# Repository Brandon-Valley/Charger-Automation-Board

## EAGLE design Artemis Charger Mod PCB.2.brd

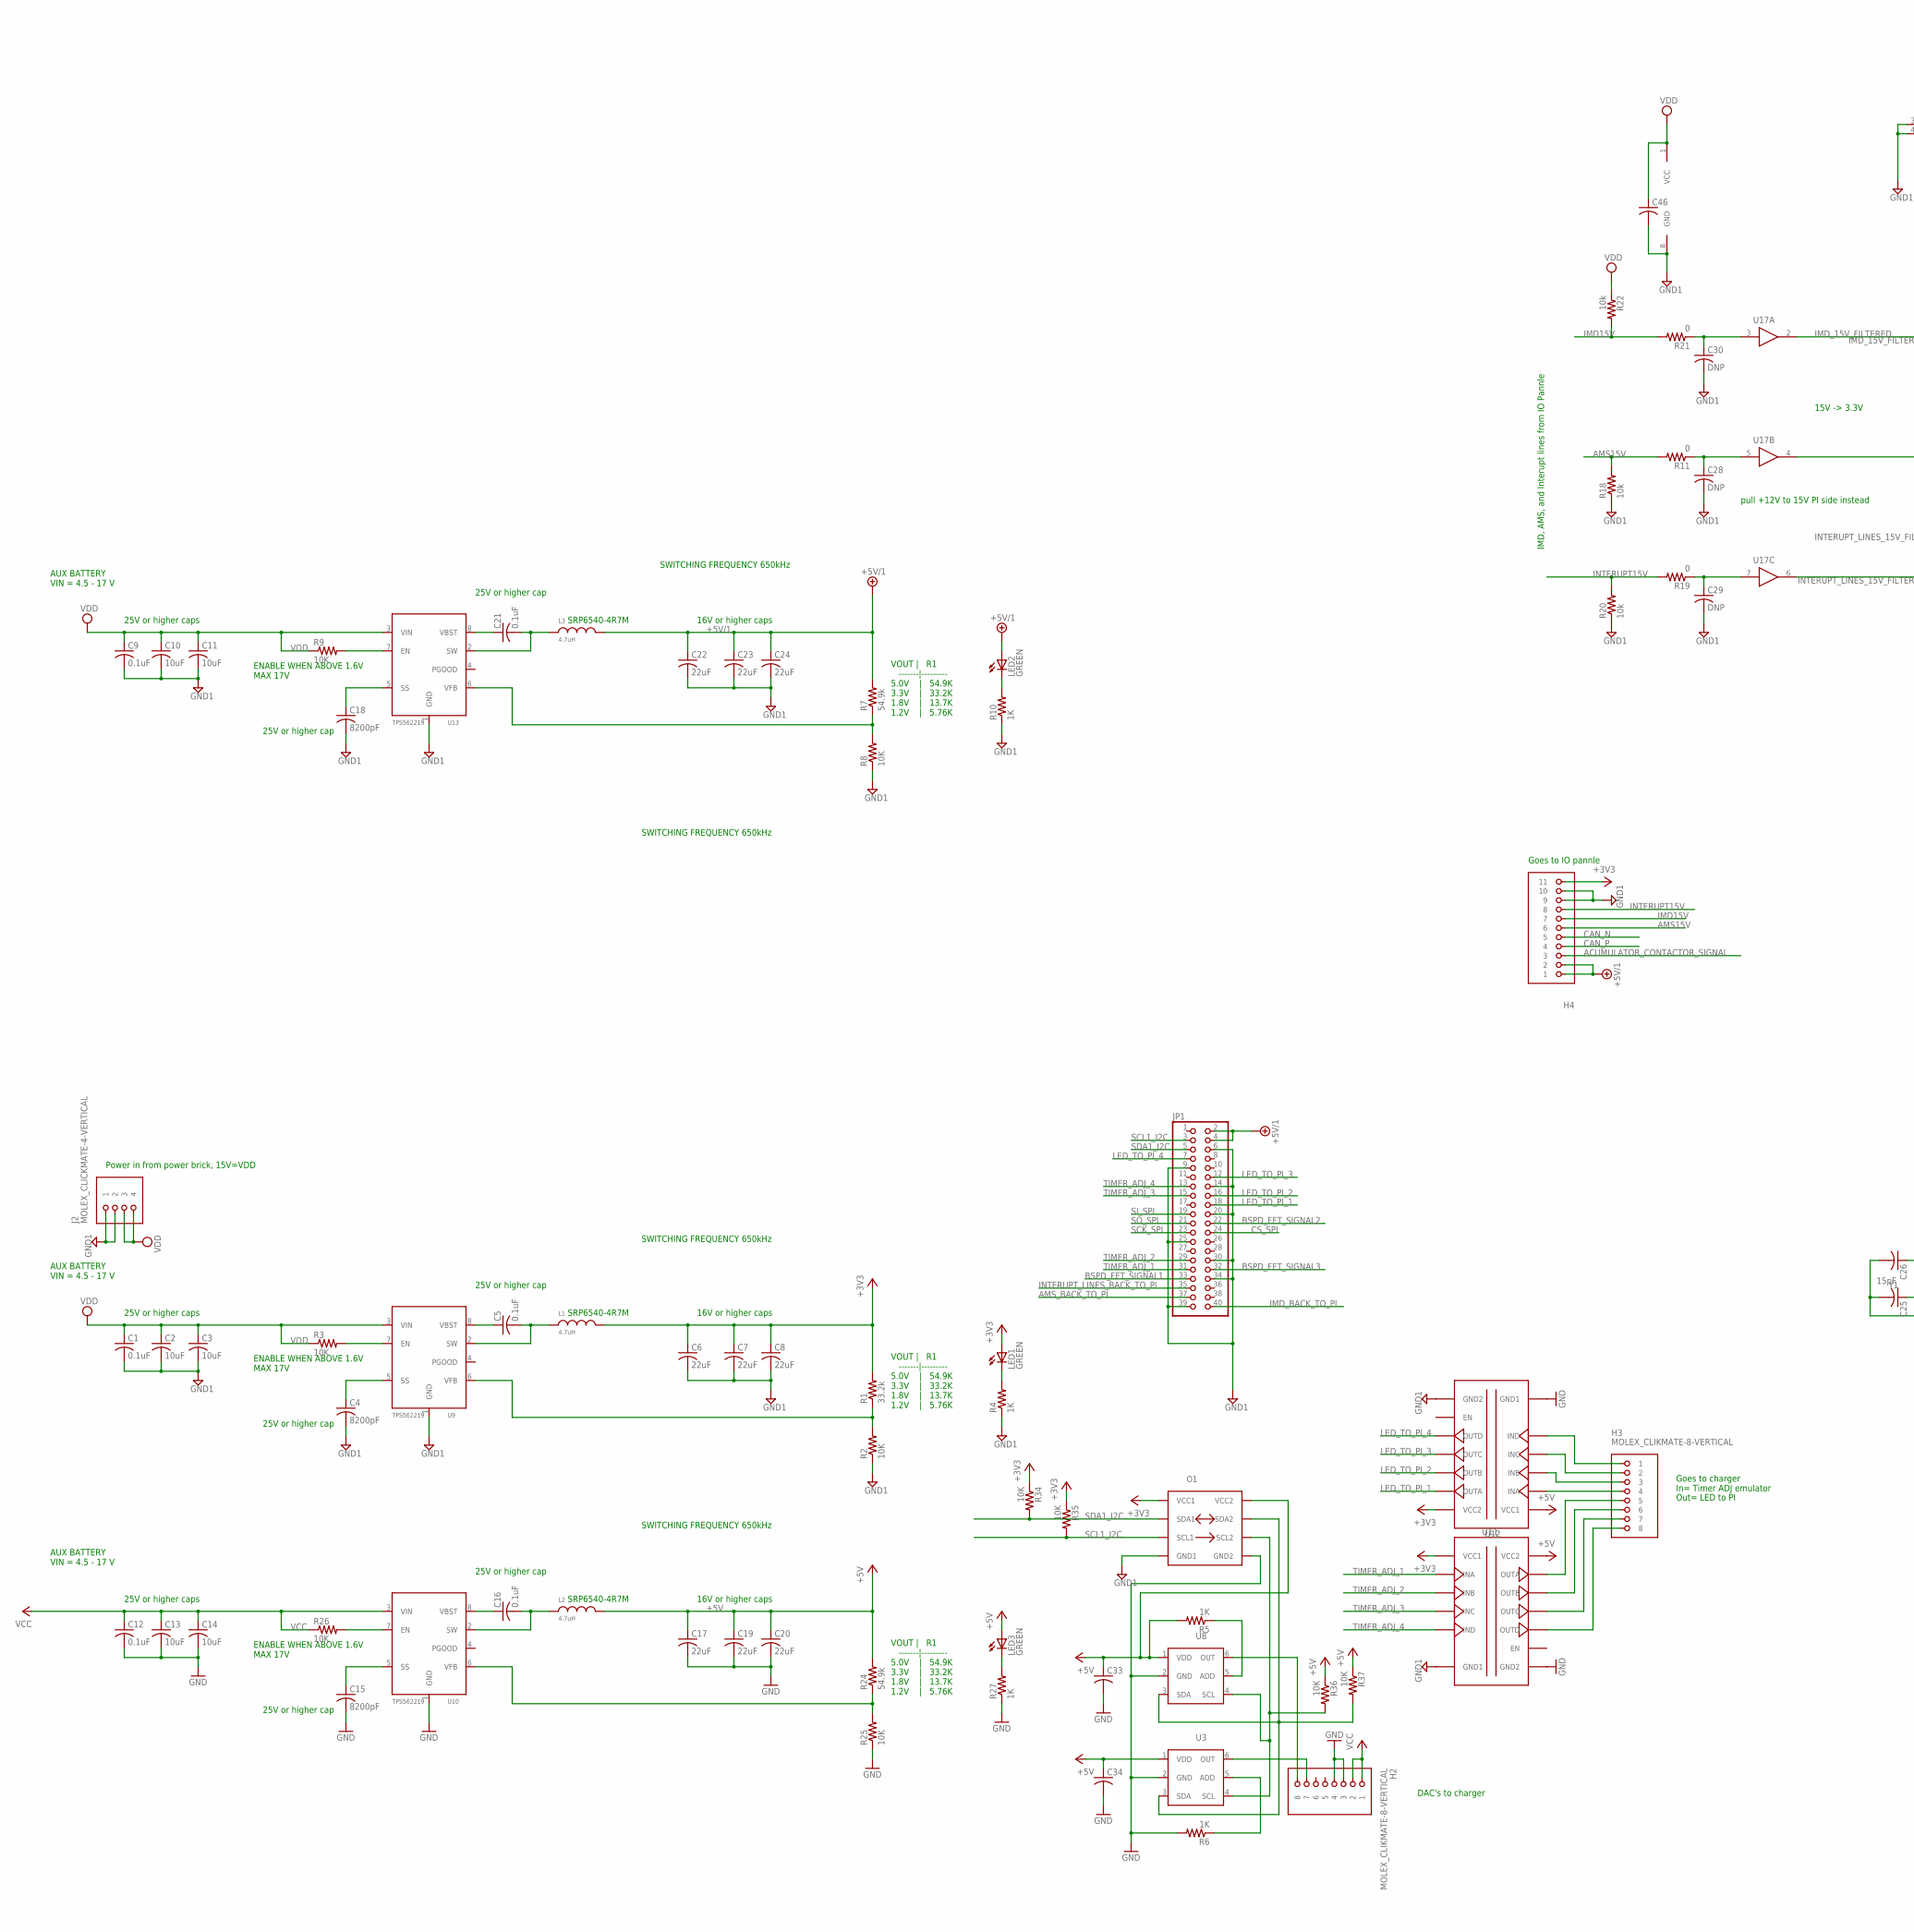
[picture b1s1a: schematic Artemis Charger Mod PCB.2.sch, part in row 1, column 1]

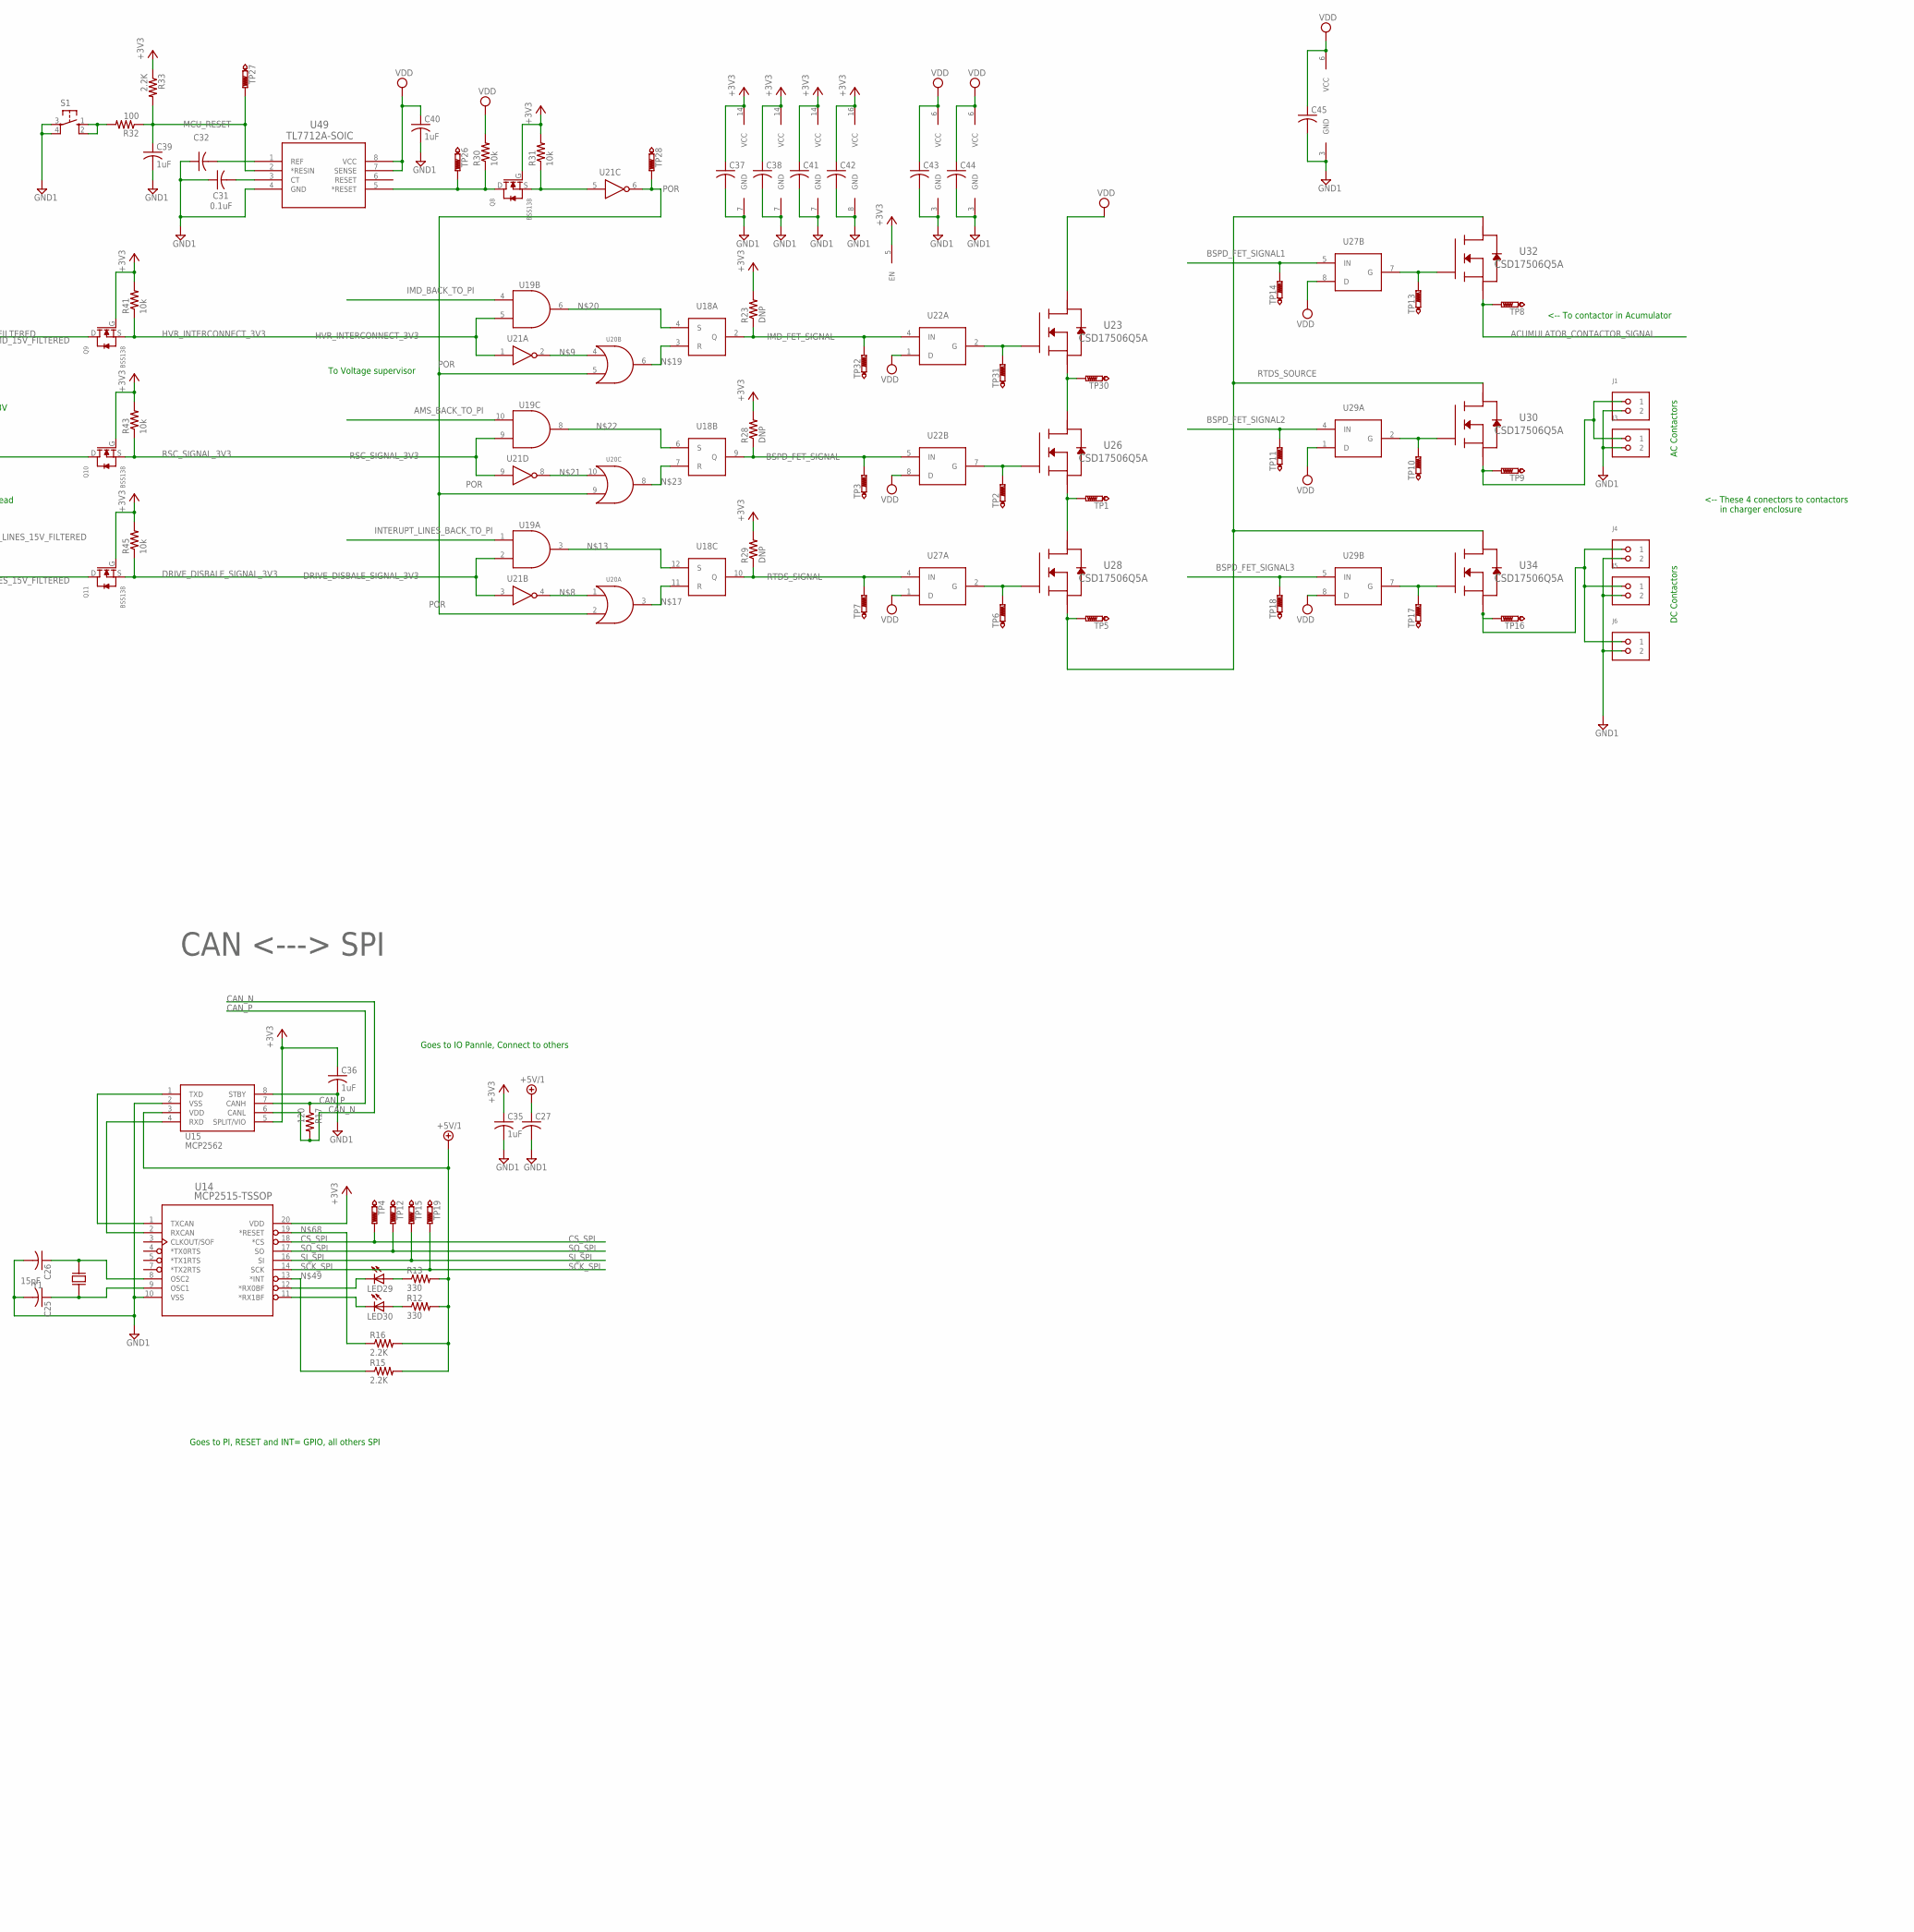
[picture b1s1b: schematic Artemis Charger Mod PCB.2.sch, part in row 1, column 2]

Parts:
C1, C5, C12, C16, C21: 0.1uF; C0805; PARTNO GRM21BR71E104KA01L
C2, C3, C10, C11, C13, C14: 10uF; C0805; PARTNO GRM21BR61E106KA73L
C4, C15, C18: 8200pF; C0805; PARTNO C0805C822K5RACTU
C6, C7, C8, C17, C19, C20, C22, C23, C24: 22uF; C0805; PARTNO C2012JB1E226M125AC
C9: 0.1uF; C0805; PARTNO 5025841170
C25, C26: 15pF; C0805; MPN 08051A150JAT2A
C27, C33, C34, C37, C38, C41, C42, C43, C44, C45, C46: 0.1uF; C0805; MPN C1005X7R1E104K050BB
C28, C29, C30: DNP; C0805
C31, C32: 0.1uF; C0805; MPN C2012X7R1H104K085AA
C35, C36, C39, C40: 1uF; C0805; PARTNO EMK212B7105KG-T
H2, H3: MOLEX_CLIKMATE-8-VERTICAL; MOLEX-CLIKMATE-8-VERTICAL-HEADER; PARTNO 5025840870
H4: MOLEX_CLICKMATE-11-VERTICAL-VERTICAL; MOLEX_CLICKMATE-11-VERTICAL-HEADER; PARTNO 5025841170
J1, J3, J4, J5, J6: MOLEX_CLICKMATE-2-VERTICAL; MOLEX-CLIKMATE-2-VERTICAL-HEADER; PARTNO 5025840270
J2: MOLEX_CLICKMATE-4-VERTICAL; MOLEX-CLIKMATE-4-VERTICAL-HEADER; PARTNO 5040500491
JP1: PINHD-2X20; 2X20; PARTNO 68602-220HLF
L1, L2, L3: 4.7uH; SRP6540; PARTNO SRP6540-4R7M
LED1, LED2, LED3: GREEN; CHIPLED_0805; PARTNO 598-8170-107F
LED29, LED30: LEDCHIP-LED0805; CHIP-LED0805; PARTNO 598-8170-107F
O1: ISO1541; PARTNO ISO1541DR
Q8, Q9, Q10, Q11: BSS138; PARTNO BSS138
R1: 33.2k; R0805; PARTNO 1676307-2
R2, R3, R8, R9, R25, R26, R34, R35, R36, R37: 10K; R0805; PARTNO ERJ-6ENF1002V
R4, R5, R6, R10, R27: 1K; R0805; PARTNO ERJ-6ENF1001V
R7, R24: 54.9k; R0805; PARTNO ERA-6AEB5492V
R11, R19, R21: 0; R0805; PARTNO ERJ-6GEY0R00V
R12, R13: 330; R0805; PARTNO ERJ-P6WF3300V
R15, R16, R33: 2.2K; R0805; PARTNO ERA-6AEB222V
R17: 120; R0805; PARTNO ERJ-6ENF1200V
R18, R20, R22, R30, R31, R41, R43, R45: 10k; R0805; PARTNO ERJ-6ENF1002V
R23, R28, R29: DNP; R0805
R32: 100; R0805; PARTNO ERJ-6ENF1000V
S1: TE-FSM4JSMATR; PARTNO FSM4JSMATR
TP1, TP2, TP3, TP4, TP5, TP6, TP7, TP8, TP9, TP10, TP11, TP12, TP13, TP14, TP15, TP16, TP17, TP18, TP19, TP26, TP27, TP28, TP30, TP31, TP32: PTR1TP20R; TP20R
U3, U8: MAX5812LEUT+TCT-ND; MAX5812; PARTNO MAX5812LEUT+T
U9, U10, U13: TPS562219; PARTNO TPS562219DDFT
U11, U12: ISO7340; ISO734X; PARTNO ISO7340CDWR
U14: MCP2515-TSSOP; TSSOP20_MC; MPN MCP2515-E/ST
U15: MCP2562; SOIC8-N_MC; MPN MCP2562-E/SN
U17: CD4050BD; SOIC-16; PARTNO CD4050BDR
U18: CD4043B; PW16-M; PARTNO CD4043BPWR
U19: SN74LVC08ASOIC; D14; PARTNO SN74LVC08ADR
U20: SN74LVC32ASOIC; D14; PARTNO SN74LVC32ADR
U21: SN74LVC04ASOIC; SOIC-14; PARTNO SN74LVC04ADR
U22, U27, U29: LTC1155; LT-SOL8; PARTNO LTC1155CS8#PBF
U23, U26, U28, U30, U32, U34: CSD17506Q5A; SON_5X6; PARTNO CSD17506Q5A
U49: TL7712A-SOIC; D8; MPN TL7705BID
Y1: CSM-3X; PARTNO ECS-160-20-3X-TR

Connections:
+3V3: C6.1, C7.1, C8.1, C35.1, C36.1, C37.1, C38.1, C41.1, C42.1, H4.11, L1.P$2, LED1.A, O1.1 (VCC1), Q8.G, Q9.G, Q10.G, Q11.G, R1.2, R23.2, R28.2, R29.2, R31.2, R33.1, R34.1, R35.1, R41.2, R43.2, R45.2, U11.P$1 (VCC1), U12.P$16 (VCC2), U14.20 (VDD), U15.5 (SPLIT/VIO), U18.5 (EN), U18.16 (VCC), U19.14 (VCC), U20.14 (VCC), U21.14 (VCC)
+5V: C17.1, C19.1, C20.1, C33.1, C34.1, L2.P$2, LED3.A, O1.8 (VCC2), R5.2, R24.2, R36.1, R37.1, U3.1 (VDD), U8.1 (VDD), U11.P$16 (VCC2), U12.P$1 (VCC1)
+5V/1: C22.1, C23.1, C24.1, C27.1, H4.1, H4.2, JP1.2, JP1.4, L3.P$2, LED2.A, R7.2, R12.2, R13.2, R15.2, R16.2, U15.3 (VDD)
ACUMULATOR_CONTACTOR_SIGNAL: H4.3, TP8.TP, U32.1 (S), U32.2 (S), U32.3 (S)
ADD: R6.1, U3.5 (ADD)
AMS15V: H4.6, R11.2, R18.2
AMS_15V_FILTERED: Q10.D, U17.4 (OUT)
AMS_BACK_TO_PI: JP1.37, U19.10 (IN1)
BSPD_FET_SIGNAL: R28.1, TP3.TP, U18.9 (Q), U22.5 (IN)
BSPD_FET_SIGNAL1: JP1.33, TP14.TP, U27.5 (IN)
BSPD_FET_SIGNAL2: JP1.22, TP11.TP, U29.4 (IN)
BSPD_FET_SIGNAL3: JP1.32, TP18.TP, U29.5 (IN)
CAN_N: H4.5, R17.2, U15.6 (CANL)
CAN_P: H4.4, R17.1, U15.7 (CANH)
CS_SPI: JP1.24, TP4.TP, U14.18 (*CS)
DRIVE_DISBALE_SIGNAL_3V3: Q11.S, R45.1, U19.2 (IN2), U21.3 (IN)
FET_CONNECT_1: TP30.TP, U23.1 (S), U23.2 (S), U23.3 (S), U26.5 (D), U26.6 (D), U26.7 (D), U26.8 (D), U26.PAD (D), U26.PAD1 (D), U26.VIA1 (D), U26.VIA2 (D), U26.VIA3 (D), U26.VIA4 (D), U26.VIA5 (D), U26.VIA6 (D), U26.VIA7 (D), U26.VIA8 (D), U26.VIA9 (D)
FET_CONNECT_2: TP1.TP, U26.1 (S), U26.2 (S), U26.3 (S), U28.5 (D), U28.6 (D), U28.7 (D), U28.8 (D), U28.PAD (D), U28.PAD1 (D), U28.VIA1 (D), U28.VIA2 (D), U28.VIA3 (D), U28.VIA4 (D), U28.VIA5 (D), U28.VIA6 (D), U28.VIA7 (D), U28.VIA8 (D), U28.VIA9 (D)
GND: C12.2, C13.2, C14.2, C15.2, C17.2, C19.2, C20.2, C33.2, C34.2, H2.3, H2.4, O1.5 (GND2), R6.2, R25.1, R27.1, U3.2 (GND), U8.2 (GND), U10.1 (GND), U11.P$9 (GND2), U11.P$15 (GND2), U12.P$2 (GND1), U12.P$8 (GND1)
GND1: C1.2, C2.2, C3.2, C4.2, C6.2, C7.2, C8.2, C9.2, C10.2, C11.2, C18.2, C22.2, C23.2, C24.2, C25.2, C26.2, C27.2, C28.2, C29.2, C30.2, C31.1, C32.1, C35.2, C36.2, C37.2, C38.2, C39.2, C40.2, C41.2, C42.2, C43.2, C44.2, C45.2, C46.2, H4.9, H4.10, J1.2, J2.1, J2.2, J3.2, J4.2, J5.2, J6.2, JP1.6, JP1.9, JP1.14, JP1.20, JP1.25, JP1.30, JP1.34, JP1.39, O1.4 (GND1), R2.1, R4.1, R8.1, R10.1, R18.1, R20.1, S1.3, S1.4, U9.1 (GND), U11.P$2 (GND1), U11.P$8 (GND1), U12.P$9 (GND2), U12.P$15 (GND2), U13.1 (GND), U14.10 (VSS), U15.2 (VSS), U15.8 (STBY), U17.8 (GND), U18.8 (GND), U19.7 (GND), U20.7 (GND), U21.7 (GND), U22.3 (GND), U27.3 (GND), U29.3 (GND), U49.4 (GND)
HVR_INTERCONNECT_3V3: Q9.S, R41.1, U19.5 (IN2), U21.1 (IN)
IMD15V: H4.7, R21.2, R22.2
IMD_15V_FILTERED: Q9.D, U17.2 (OUT)
IMD_BACK_TO_PI: JP1.40, U19.4 (IN1)
IMD_FET_SIGNAL: R23.1, TP32.TP, U18.2 (Q), U22.4 (IN)
INTERUPT15V: H4.8, R19.2, R20.2
INTERUPT_LINES_15V_FILTERED: Q11.D, U17.6 (OUT)
INTERUPT_LINES_BACK_TO_PI: JP1.35, U19.1 (IN1)
LED_TO_PI_1: JP1.18, U12.P$14 (OUTA)
LED_TO_PI_1_C: H3.1, U12.P$6 (IND)
LED_TO_PI_2: JP1.16, U12.P$13 (OUTB)
LED_TO_PI_2_C: H3.2, U12.P$5 (INC)
LED_TO_PI_3: JP1.12, U12.P$12 (OUTC)
LED_TO_PI_3_C: H3.3, U12.P$4 (INB)
LED_TO_PI_4: JP1.7, U12.P$11 (OUTD)
LED_TO_PI_4_C: H3.4, U12.P$3 (INA)
MCU_RESET: C39.1, R32.1, R33.2, TP27.TP, U49.2 (*RESIN)
unnamed: R3.2, U9.7 (EN)
unnamed: LED1.C, R4.2
unnamed: R5.1, U8.5 (ADD)
unnamed: J4.1, J5.1, J6.1, TP16.TP, U34.1 (S), U34.2 (S), U34.3 (S)
unnamed: U20.1 (IN1), U21.4 (OUT)
unnamed: U20.4 (IN1), U21.2 (OUT)
unnamed: U18.12 (S), U19.3 (OUT)
unnamed: U18.11 (R), U20.3 (OUT)
unnamed: U18.3 (R), U20.6 (OUT)
unnamed: U18.4 (S), U19.6 (OUT)
unnamed: U20.10 (IN1), U21.8 (OUT)
unnamed: U18.6 (S), U19.8 (OUT)
unnamed: U18.7 (R), U20.8 (OUT)
unnamed: H2.7, U3.6 (OUT)
unnamed: H2.8, U8.6 (OUT)
unnamed: LED3.C, R27.2
unnamed: H3.5, U11.P$14 (OUTA)
unnamed: H3.6, U11.P$13 (OUTB)
unnamed: H3.7, U11.P$12 (OUTC)
unnamed: H3.8, U11.P$11 (OUTD)
unnamed: C28.1, R11.1, U17.5 (IN)
unnamed: R9.2, U13.7 (EN)
unnamed: LED2.C, R10.2
unnamed: U14.2 (RXCAN), U15.4 (RXD)
unnamed: U14.1 (TXCAN), U15.1 (TXD)
unnamed: R15.1, U14.13 (*INT)
unnamed: C29.1, R19.1, U17.7 (IN)
unnamed: C30.1, R21.1, U17.3 (IN)
unnamed: TP31.TP, U22.2 (G), U23.4 (G)
unnamed: TP2.TP, U22.7 (G), U26.4 (G)
unnamed: TP6.TP, U27.2 (G), U28.4 (G)
unnamed: TP10.TP, U29.2 (G), U30.4 (G)
unnamed: Q8.S, R31.1, U21.5 (IN)
unnamed: TP13.TP, U27.7 (G), U32.4 (G)
unnamed: Q8.D, R30.1, TP26.TP, U49.5 (*RESET)
unnamed: R32.2, S1.1, S1.2
unnamed: TP17.TP, U29.7 (G), U34.4 (G)
unnamed: R16.1, U14.19 (*RESET)
unnamed: LED30.C, U14.11 (*RX1BF)
unnamed: LED29.C, U14.12 (*RX0BF)
unnamed: LED30.A, R12.1
unnamed: LED29.A, R13.1
unnamed: C26.1, U14.8 (OSC2), Y1.P$1
unnamed: C25.1, U14.9 (OSC1), Y1.P$2
unnamed: C31.2, U49.3 (CT)
unnamed: C32.2, U49.1 (REF)
unnamed: R26.2, U10.7 (EN)
POR: TP28.TP, U20.2 (IN2), U20.5 (IN2), U20.9 (IN2), U21.6 (OUT)
RSC_SIGNAL_3V3: Q10.S, R43.1, U19.9 (IN2), U21.9 (IN)
RTDS_SIGNAL: R29.1, TP7.TP, U18.10 (Q), U27.4 (IN)
RTDS_SOURCE: TP5.TP, U28.1 (S), U28.2 (S), U28.3 (S), U30.5 (D), U30.6 (D), U30.7 (D), U30.8 (D), U30.PAD (D), U30.PAD1 (D), U30.VIA1 (D), U30.VIA2 (D), U30.VIA3 (D), U30.VIA4 (D), U30.VIA5 (D), U30.VIA6 (D), U30.VIA7 (D), U30.VIA8 (D), U30.VIA9 (D), U32.5 (D), U32.6 (D), U32.7 (D), U32.8 (D), U32.PAD (D), U32.PAD1 (D), U32.VIA1 (D), U32.VIA2 (D), U32.VIA3 (D), U32.VIA4 (D), U32.VIA5 (D), U32.VIA6 (D), U32.VIA7 (D), U32.VIA8 (D), U32.VIA9 (D), U34.5 (D), U34.6 (D), U34.7 (D), U34.8 (D), U34.PAD (D), U34.PAD1 (D), U34.VIA1 (D), U34.VIA2 (D), U34.VIA3 (D), U34.VIA4 (D), U34.VIA5 (D), U34.VIA6 (D), U34.VIA7 (D), U34.VIA8 (D), U34.VIA9 (D)
RTDS_SOURCE1: J1.1, J3.1, TP9.TP, U30.1 (S), U30.2 (S), U30.3 (S)
SCK_SPI: JP1.23, TP19.TP, U14.14 (SCK)
SCL: O1.6 (SCL2), R36.2, U3.4 (SCL), U8.4 (SCL)
SCL1_I2C: JP1.3, O1.3 (SCL1), R35.2
SDA: O1.7 (SDA2), R37.2, U3.3 (SDA), U8.3 (SDA)
SDA1_I2C: JP1.5, O1.2 (SDA1), R34.2
SI_SPI: JP1.19, TP15.TP, U14.16 (SI)
SO_SPI: JP1.21, TP12.TP, U14.17 (SO)
SS_3V3: C4.1, U9.5 (SS)
SS_5V: C15.1, U10.5 (SS)
SS_5V2: C18.1, U13.5 (SS)
SW_3V3: C5.2, L1.P$1, U9.2 (SW)
SW_5V: C16.2, L2.P$1, U10.2 (SW)
SW_5V/1: C21.2, L3.P$1, U13.2 (SW)
TIMER_ADJ_1: JP1.31, U11.P$3 (INA)
TIMER_ADJ_2: JP1.29, U11.P$4 (INB)
TIMER_ADJ_3: JP1.15, U11.P$5 (INC)
TIMER_ADJ_4: JP1.13, U11.P$6 (IND)
VBST_3V3: C5.1, U9.8 (VBST)
VBST_5V: C16.1, U10.8 (VBST)
VBST_5V/1: C21.1, U13.8 (VBST)
VCC: C12.1, C13.1, C14.1, H2.1, H2.2, R26.1, U10.3 (VIN)
VDD: C1.1, C2.1, C3.1, C9.1, C10.1, C11.1, C40.1, C43.1, C44.1, C45.1, C46.1, J2.3, J2.4, R3.1, R9.1, R22.1, R30.2, U9.3 (VIN), U13.3 (VIN), U17.1 (VCC), U22.1 (D), U22.6 (VCC), U22.8 (D), U23.5 (D), U23.6 (D), U23.7 (D), U23.8 (D), U23.PAD (D), U23.PAD1 (D), U23.VIA1 (D), U23.VIA2 (D), U23.VIA3 (D), U23.VIA4 (D), U23.VIA5 (D), U23.VIA6 (D), U23.VIA7 (D), U23.VIA8 (D), U23.VIA9 (D), U27.1 (D), U27.6 (VCC), U27.8 (D), U29.1 (D), U29.6 (VCC), U29.8 (D), U49.7 (SENSE), U49.8 (VCC)
VFB_3V3: R1.1, R2.2, U9.6 (VFB)
VFB_5V: R24.1, R25.2, U10.6 (VFB)
VFB_5V/1: R7.1, R8.2, U13.6 (VFB)

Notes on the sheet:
AUX BATTERY VIN = 4.5 - 17 V
VOUT | R1 -------|--------- 5.0V | 54.9K 3.3V | 33.2K 1.8V | 13.7K 1.2V | 5.76K
SRP6540-4R7M
SWITCHING FREQUENCY 650kHz
ENABLE WHEN ABOVE 1.6V MAX 17V
25V or higher caps
25V or higher cap
16V or higher caps
Goes to IO Pannle, Connect to others
Goes to charger In= Timer ADJ emulator
Out= LED to PI
Power in from power brick, 15V=VDD
DAC's to charger
Goes to IO pannle
Goes to PI, RESET and INT= GPIO, all others SPI
pull +12V to 15V PI side instead
15V -> 3.3V
To Voltage supervisor
IMD, AMS, and Interupt lines from IO Pannle
<-- These 4 conectors to contactors in charger enclosure
<-- To contactor in Acumulator
CAN <---> SPI
DC Contactors
AC Contactors

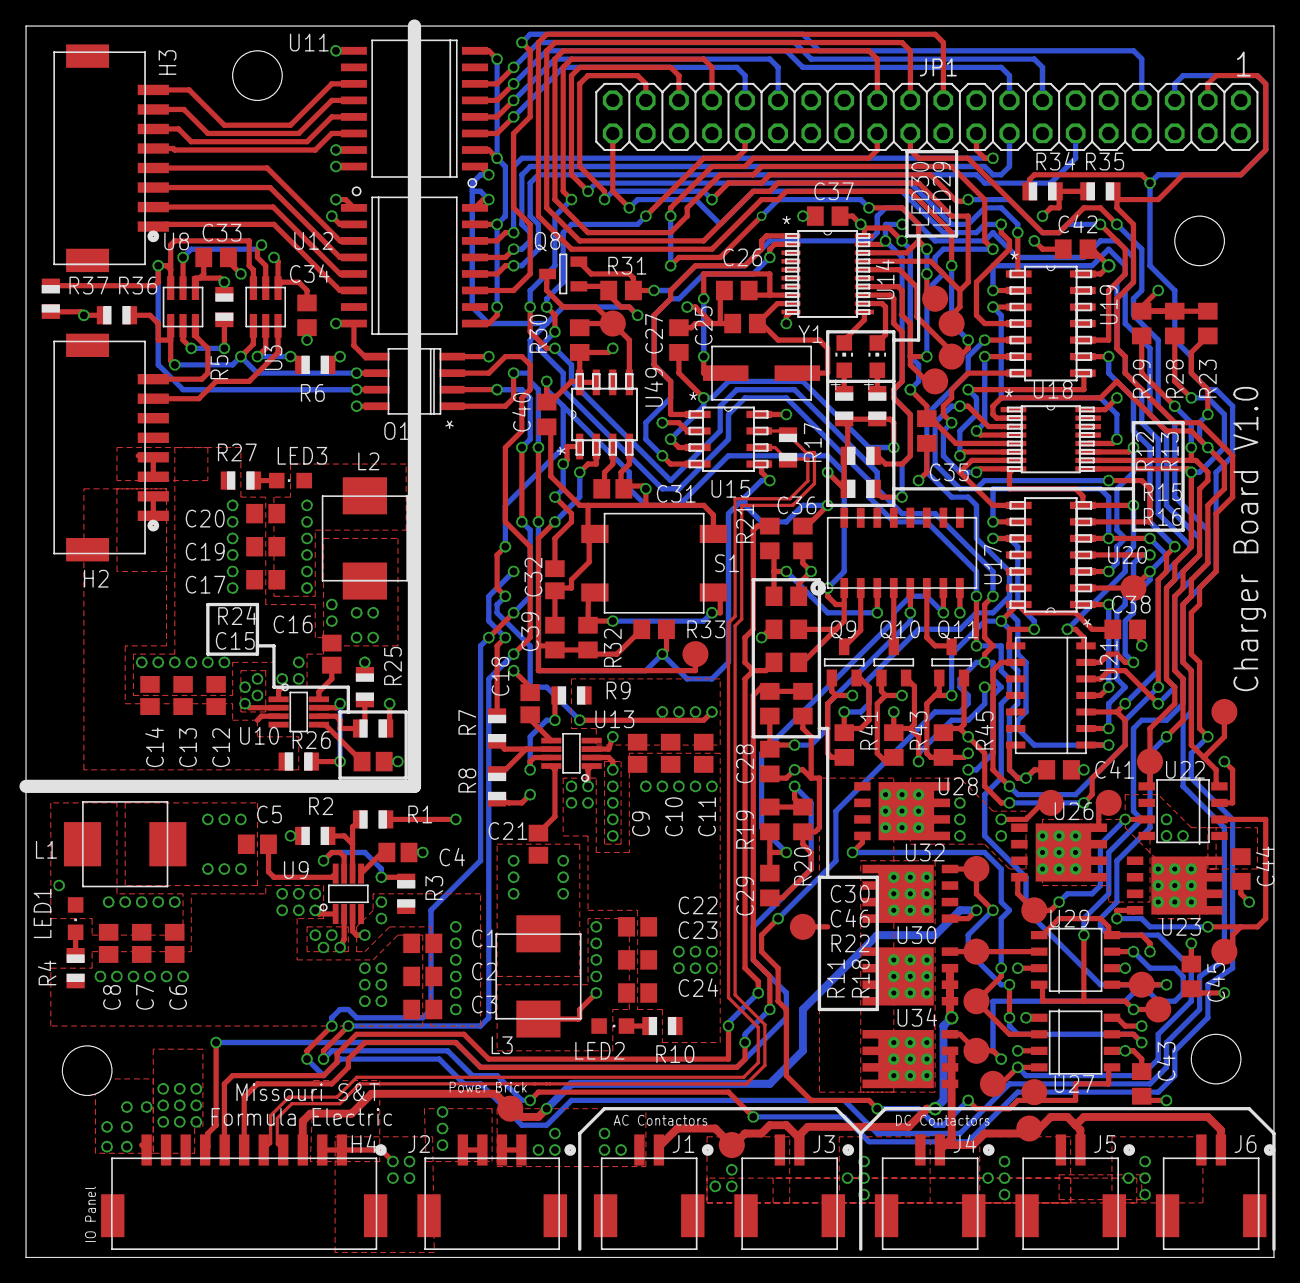
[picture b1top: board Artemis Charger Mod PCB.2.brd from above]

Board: 4 copper layers, 95.9 x 94.6 mm, 159 parts (0 on the bottom side), 114 nets.

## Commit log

2015-11-28 Artemis Charger Mod PCB: Modification to the Manzanita Micro PFC Charger: Allows for remote control of the charger, removing the need for the knobs // Also includes connection between the Raspberry P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
2015-12-30 Almost Done
2015-12-30 DONE
2015-12-31 Added BOM
2016-01-04 Fixed list of errors: Too many vias around regulators
    Make +5V plane in cover all area in isolated region
    Make isolation barrier a simple rectangle
    rotate +5v regulator (isolated area) 180deg so that the current path is more direct
    More vias/planes at connectors
    Give nets a descriptive name
    Use vector font
2016-01-07 Started cleaning up layout
2016-01-07 Fixed second list of errors: Decoupling capacitors
    U11/12 EN pin is floating
    Don't use solid planes at FET drivers
    Lots of random vias
    Planes from FETs to contactor connector
    Connector labels
    Cleanup supply layer planes
2016-01-07 Fixed LED Silkscreens
2016-01-08 Added extra contactor for charger discharge
2016-01-12 Fixed fixed silk screens, fixed a few overlap errors
2016-01-20 Fixed crooked supply planes, moved planes away from isolation line, made better silkscreens, about to do BOM
2016-01-20 Added molex 1 pin and 2X20 header to BOM
2016-01-21 Changes supply Plane
2016-01-21 Added CAM Files
2016-01-29 Added STENCIL
2016-01-29 Added STENCIL and cleaned up folder
2016-02-05 Added DXF
2016-04-18 Update gitignore
2016-09-07 Cleaned up sch
